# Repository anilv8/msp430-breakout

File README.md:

# MSP430 Breakout

Simple reakout bord for MSP430G25553.

# Schematic of circuit

## ERC Result

# PCB Board
### Front Copper

### Back copper

## DRC Result

## 3D view of PCB
### Front:

### Back:

## Gerber
### Front Copper

### Back Copper

# BOM
| Item |	Qty |	Reference(s)	| Value	| LibPart |	Footprint |	Datasheet |
| ---- | ---- | ---- | ---- | ---- | ---- | ---- |
| 1 |	1	| C1	| 1u	| Device:C |	Capacitor_SMD:C_0603_1608Metric_Pad1.08x0.95mm_HandSolder |	~ |
| 2 |	2	| C2, C3	| 10u	| Device:C	| Capacitor_SMD:C_0603_1608Metric_Pad1.08x0.95mm_HandSolder	| ~ |
| 3 |	1 |	C4	| 10n |	Device:C	| Capacitor_SMD:C_0603_1608Metric_Pad1.08x0.95mm_HandSolder	| ~ |
| 4	| 2	| D1, D2	| LED | Device:LED |	LED_SMD:LED_0603_1608Metric_Pad1.05x0.95mm_HandSolder |	~ |
| 5	| 2	| J1, J2	| Conn_01x10	| Connector_Generic:Conn_01x10	| Connector_PinHeader_2.54mm:PinHeader_1x10_P2.54mm_Vertical |	~ |
| 6	| 1	| J3	| USB_B_Mini	| Connector:USB_B_Mini |	Connector_USB:USB_Mini-B_Wuerth_65100516121_Horizontal |	~ |
| 7	| 2	| R1, R2	| 100	| Device:R	| Resistor_SMD:R_0603_1608Metric_Pad0.98x0.95mm_HandSolder |	~ |
| 8	| 1	| R3	| 47k	| Device:R	| Resistor_SMD:R_0603_1608Metric_Pad0.98x0.95mm_HandSolder	| ~ |
| 9	| 1	| SW1	| SW_Push	| Switch:SW_Push |	Button_Switch_THT:SW_TH_Tactile_Omron_B3F-10xx |	~ |
| 10	| 1	| U1	| MSP430G2553IPW20	| MCU_Texas_MSP430:MSP430G2553IPW20	Package_DIP:DIP-20_W7.62mm_Socket |	http://www.ti.com/lit/ds/symlink/msp430g2553.pdf |
| 11	| 1	| U2	| AMS1117-3.3	| Regulator_Linear:AMS1117-3.3	| Package_TO_SOT_SMD:SOT-223-3_TabPin2 |	http://www.advanced-monolithic.com/pdf/ds1117.pdf |

# REFERENCES
[1]  https://github.com/akowalczyk18/Kicad/tree/master/1-Hour-Board/1-Hour-Board

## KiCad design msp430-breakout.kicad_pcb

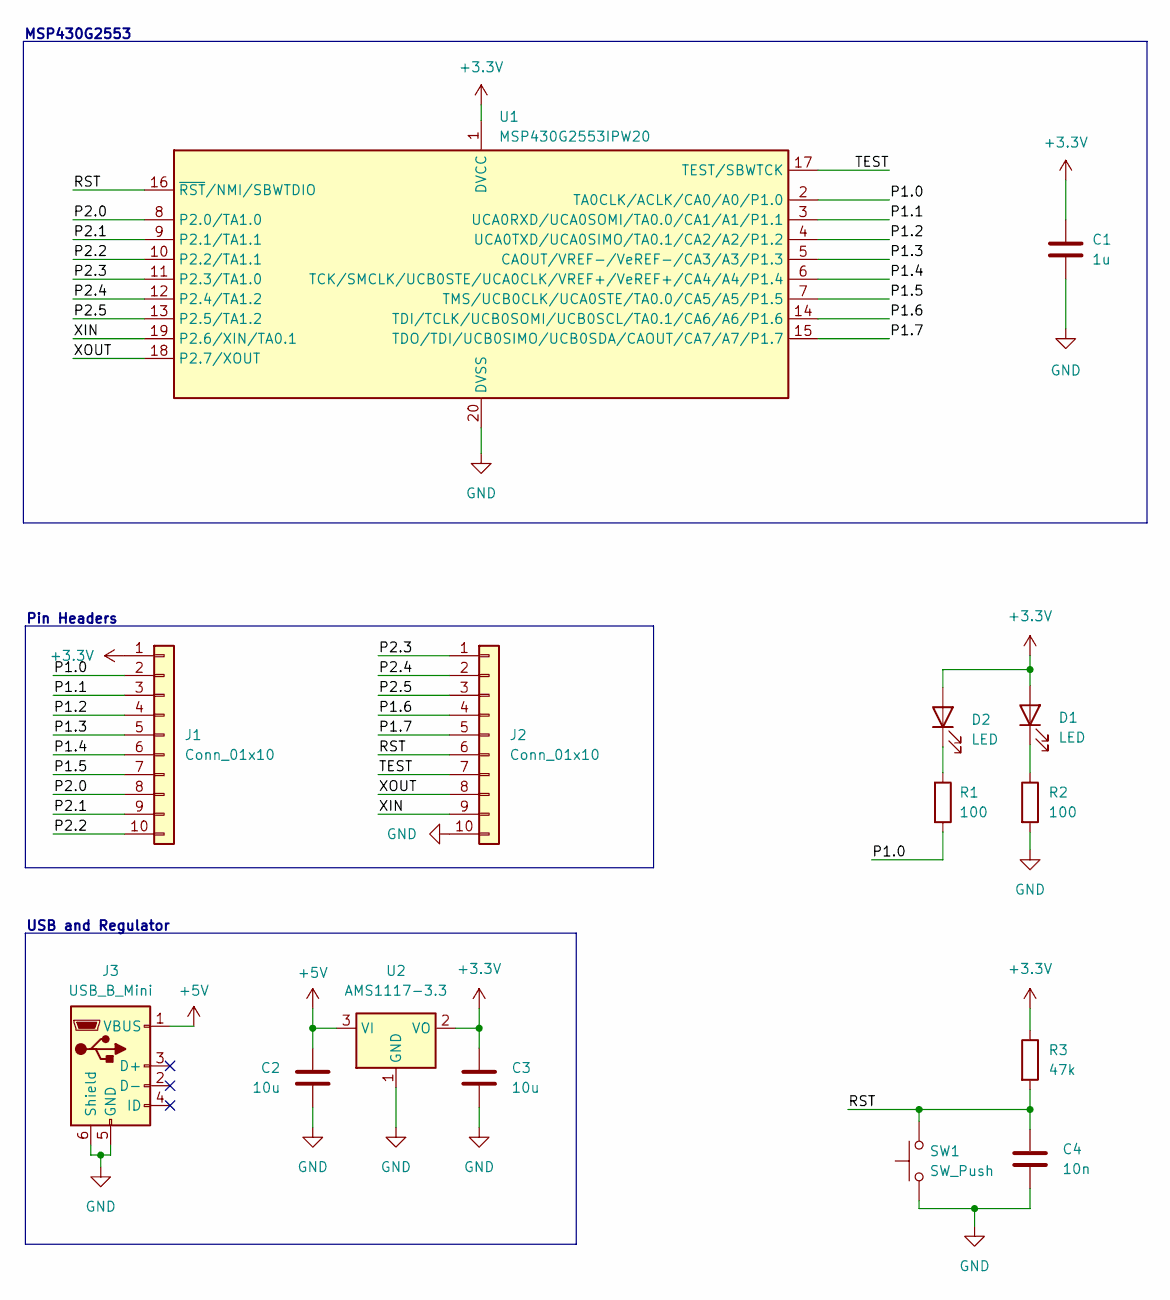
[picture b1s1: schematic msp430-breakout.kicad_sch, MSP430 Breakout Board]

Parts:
C1: 1u; C_0603_1608Metric_Pad1.08x0.95mm_HandSolder
C2, C3: 10u; C_0603_1608Metric_Pad1.08x0.95mm_HandSolder
C4: 10n; C_0603_1608Metric_Pad1.08x0.95mm_HandSolder
D1, D2: LED; LED_0603_1608Metric_Pad1.05x0.95mm_HandSolder
J1, J2: Conn_01x10; PinHeader_1x10_P2.54mm_Vertical
J3: USB_B_Mini; USB_Mini-B_Wuerth_65100516121_Horizontal
R1, R2: 100; R_0603_1608Metric_Pad0.98x0.95mm_HandSolder
R3: 47k; R_0603_1608Metric_Pad0.98x0.95mm_HandSolder
SW1: SW_Push; SW_TH_Tactile_Omron_B3F-10xx
U1: MSP430G2553IPW20; DIP-20_W7.62mm_Socket
U2: AMS1117-3.3; SOT-223-3_TabPin2

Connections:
+3.3V: C1.1, C3.2, D1.2 (A), D2.2 (A), J1.1, R3.1, U1.1 (DVCC), U2.2 (VO)
+5V: C2.2, J3.1 (VBUS), U2.3 (VI)
/P1.0: J1.2, R1.2, U1.2 (TA0CLK/ACLK/CA0/A0/P1.0)
/P1.1: J1.3, U1.3 (UCA0RXD/UCA0SOMI/TA0.0/CA1/A1/P1.1)
/P1.2: J1.4, U1.4 (UCA0TXD/UCA0SIMO/TA0.1/CA2/A2/P1.2)
/P1.3: J1.5, U1.5 (CAOUT/VREF-/VeREF-/CA3/A3/P1.3)
/P1.4: J1.6, U1.6 (TCK/SMCLK/UCB0STE/UCA0CLK/VREF+/VeREF+/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)
/P1.5: J1.7, U1.7 (TMS/UCB0CLK/UCA0STE/TA0.0/CA5/A5/P1.5)
/P1.6: J2.4, U1.14 (TDI/TCLK/UCB0SOMI/UCB0SCL/TA0.1/CA6/A6/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)
/P1.7: J2.5, U1.15 (TDO/TDI/UCB0SIMO/UCB0SDA/CAOUT/CA7/A7/P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)
/P2.0: J1.8, U1.8 (P2.0/TA1.0)
/P2.1: J1.9, U1.9 (P2.1/TA1.1)
/P2.2: J1.10, U1.10 (P2.2/TA1.1)
/P2.3: J2.1, U1.11 (P2.3/TA1.0)
/P2.4: J2.2, U1.12 (P2.4/TA1.2)
/P2.5: J2.3, U1.13 (P2.5/TA1.2)
/RST: C4.2, J2.6, R3.2, SW1.2, U1.16 (~RST/NMI/SBWTDIO)
/TEST: J2.7, U1.17 (TEST/SBWTCK)
/XIN: J2.9, U1.19 (P2.6/XIN/TA0.1)
/XOUT: J2.8, U1.18 (P2.7/XOUT)
GND: C1.2, C2.1, C3.1, C4.1, J2.10, J3.5 (GND), J3.6 (Shield), R2.2, SW1.1, U1.20 (DVSS), U2.1 (GND)
unnamed: D1.1 (K), R2.1
unnamed: D2.1 (K), R1.1

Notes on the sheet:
MSP430G2553
USB and Regulator
Pin Headers

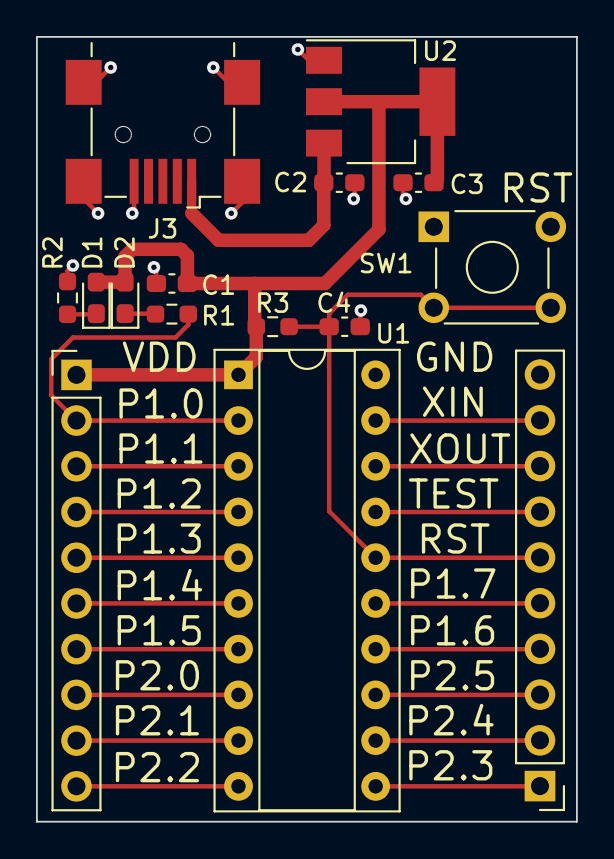
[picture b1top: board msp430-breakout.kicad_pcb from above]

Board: 2 copper layers, 30.0 x 43.6 mm, 15 parts (0 on the bottom side), 23 nets.
